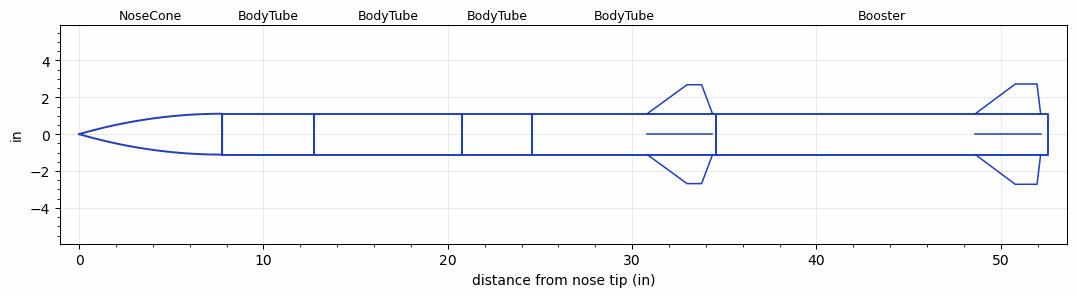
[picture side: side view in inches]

<RASAeroDocument>
 <FileVersion>2</FileVersion>
 <RocketDesign>
  <NoseCone>
   <Length>7.7579</Length>
   <Diameter>2.217</Diameter>
   <Shape>Tangent Ogive</Shape>
   <Location>0</Location>
  </NoseCone>
  <BodyTube>
   <Length>5</Length>
   <Diameter>2.217</Diameter>
   <Location>7.7579</Location>
  </BodyTube>
  <BodyTube>
   <Length>8</Length>
   <Diameter>2.217</Diameter>
   <Location>12.7578</Location>
  </BodyTube>
  <BodyTube>
   <Length>3.8</Length>
   <Diameter>2.217</Diameter>
   <Location>20.7578</Location>
  </BodyTube>
  <BodyTube>
   <Length>10</Length>
   <Diameter>2.217</Diameter>
   <Location>24.5578</Location>
   <Fin>
    <Count>4</Count>
    <Chord>3.5433</Chord>
    <Span>1.5748</Span>
    <SweepDistance>2.1653</SweepDistance>
    <TipChord>0.7874</TipChord>
    <Thickness>0.1181</Thickness>
    <Location>3.7401</Location>
    <AirfoilSection>Rounded</AirfoilSection>
   </Fin>
  </BodyTube>
  <Booster>
   <Length>18</Length>
   <Diameter>2.217</Diameter>
   <InsideDiameter>2.217</InsideDiameter>
   <Location>34.5578</Location>
   <ShoulderLength>0</ShoulderLength>
   <Fin>
    <Count>4</Count>
    <Chord>3.5433</Chord>
    <Span>1.6117</Span>
    <SweepDistance>2.1653</SweepDistance>
    <TipChord>1.1811</TipChord>
    <Thickness>0.1181</Thickness>
    <Location>3.937</Location>
    <AirfoilSection>Rounded</AirfoilSection>
   </Fin>
  </Booster>
  <Surface>Rough Camouflage Paint</Surface>
  <ModifiedBarrowman>False</ModifiedBarrowman>
  <Turbulence>False</Turbulence>
  <UseBooster1>True</UseBooster1>
  <UseBooster2>False</UseBooster2>
 </RocketDesign>
 <LaunchSite>
  <Altitude>0</Altitude>
  <Pressure>29.9214</Pressure>
  <RodAngle>0</RodAngle>
  <RodLength>39.37</RodLength>
  <Temperature>59</Temperature>
  <WindSpeed>4.4739</WindSpeed>
 </LaunchSite>
 <Recovery>
  <Altitude1>656.168</Altitude1>
  <Altitude2>656.168</Altitude2>
  <DeviceType1>Parachute</DeviceType1>
  <DeviceType2>Parachute</DeviceType2>
  <Event1>True</Event1>
  <Event2>True</Event2>
  <Size1>24</Size1>
  <Size2>9</Size2>
  <EventType1>Altitude</EventType1>
  <EventType2>Apogee</EventType2>
  <CD1>0.8</CD1>
  <CD2>0</CD2>
 </Recovery>
 <SimulationList>
  <Simulation>
   <SustainerEngine>G33-MY-9A  (CTI)</SustainerEngine>
   <SustainerLaunchWt>1.65</SustainerLaunchWt>
   <SustainerNozzleDiameter>2</SustainerNozzleDiameter>
   <SustainerCG>20.86</SustainerCG>
   <SustainerIgnitionDelay>5</SustainerIgnitionDelay>
   <Booster1Engine>G125-RL  (CTI)</Booster1Engine>
   <Booster1LaunchWt>2.53</Booster1LaunchWt>
   <Booster1SeparationDelay>2</Booster1SeparationDelay>
   <Booster1IgnitionDelay>0</Booster1IgnitionDelay>
   <Booster1CG>29.49</Booster1CG>
   <Booster1NozzleDiameter>2</Booster1NozzleDiameter>
   <IncludeBooster1>True</IncludeBooster1>
   <Booster2Delay>0</Booster2Delay>
   <IncludeBooster2>False</IncludeBooster2>
   <TimetoApogee>25.2104</TimetoApogee>
   <MaxAltitude>7204.09</MaxAltitude>
   <MaxVelocity>732.7067</MaxVelocity>
  </Simulation>
  <Simulation>
   <SustainerLaunchWt>1.3933</SustainerLaunchWt>
   <SustainerCG>18.9759</SustainerCG>
   <SustainerIgnitionDelay>0</SustainerIgnitionDelay>
   <Booster1LaunchWt>1.8447</Booster1LaunchWt>
   <Booster1SeparationDelay>0</Booster1SeparationDelay>
   <Booster1IgnitionDelay>0</Booster1IgnitionDelay>
   <Booster1CG>24.7695</Booster1CG>
   <IncludeBooster1>True</IncludeBooster1>
   <Booster2Delay>0</Booster2Delay>
   <IncludeBooster2>False</IncludeBooster2>
  </Simulation>
 </SimulationList>
</RASAeroDocument>
